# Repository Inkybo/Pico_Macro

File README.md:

# Pico_Macro Keypad

Pico_Macro is 3*2 keys plus two rotary encoders w/ push button as well as a 128x32 OLED screen and trackball. 

## Firmware

Pico_Macro uses [KMK firmware](http://kmkfw.info)

The code.py file contains a basic template for configureing the keys and the optional pimoroni trackback

## Images

The bare pcb: 

Populated board

/w Keys 

## TODO

- [x] add pictures to readme
- [ ] configure screen to work
- [ ] add support for kailh choc

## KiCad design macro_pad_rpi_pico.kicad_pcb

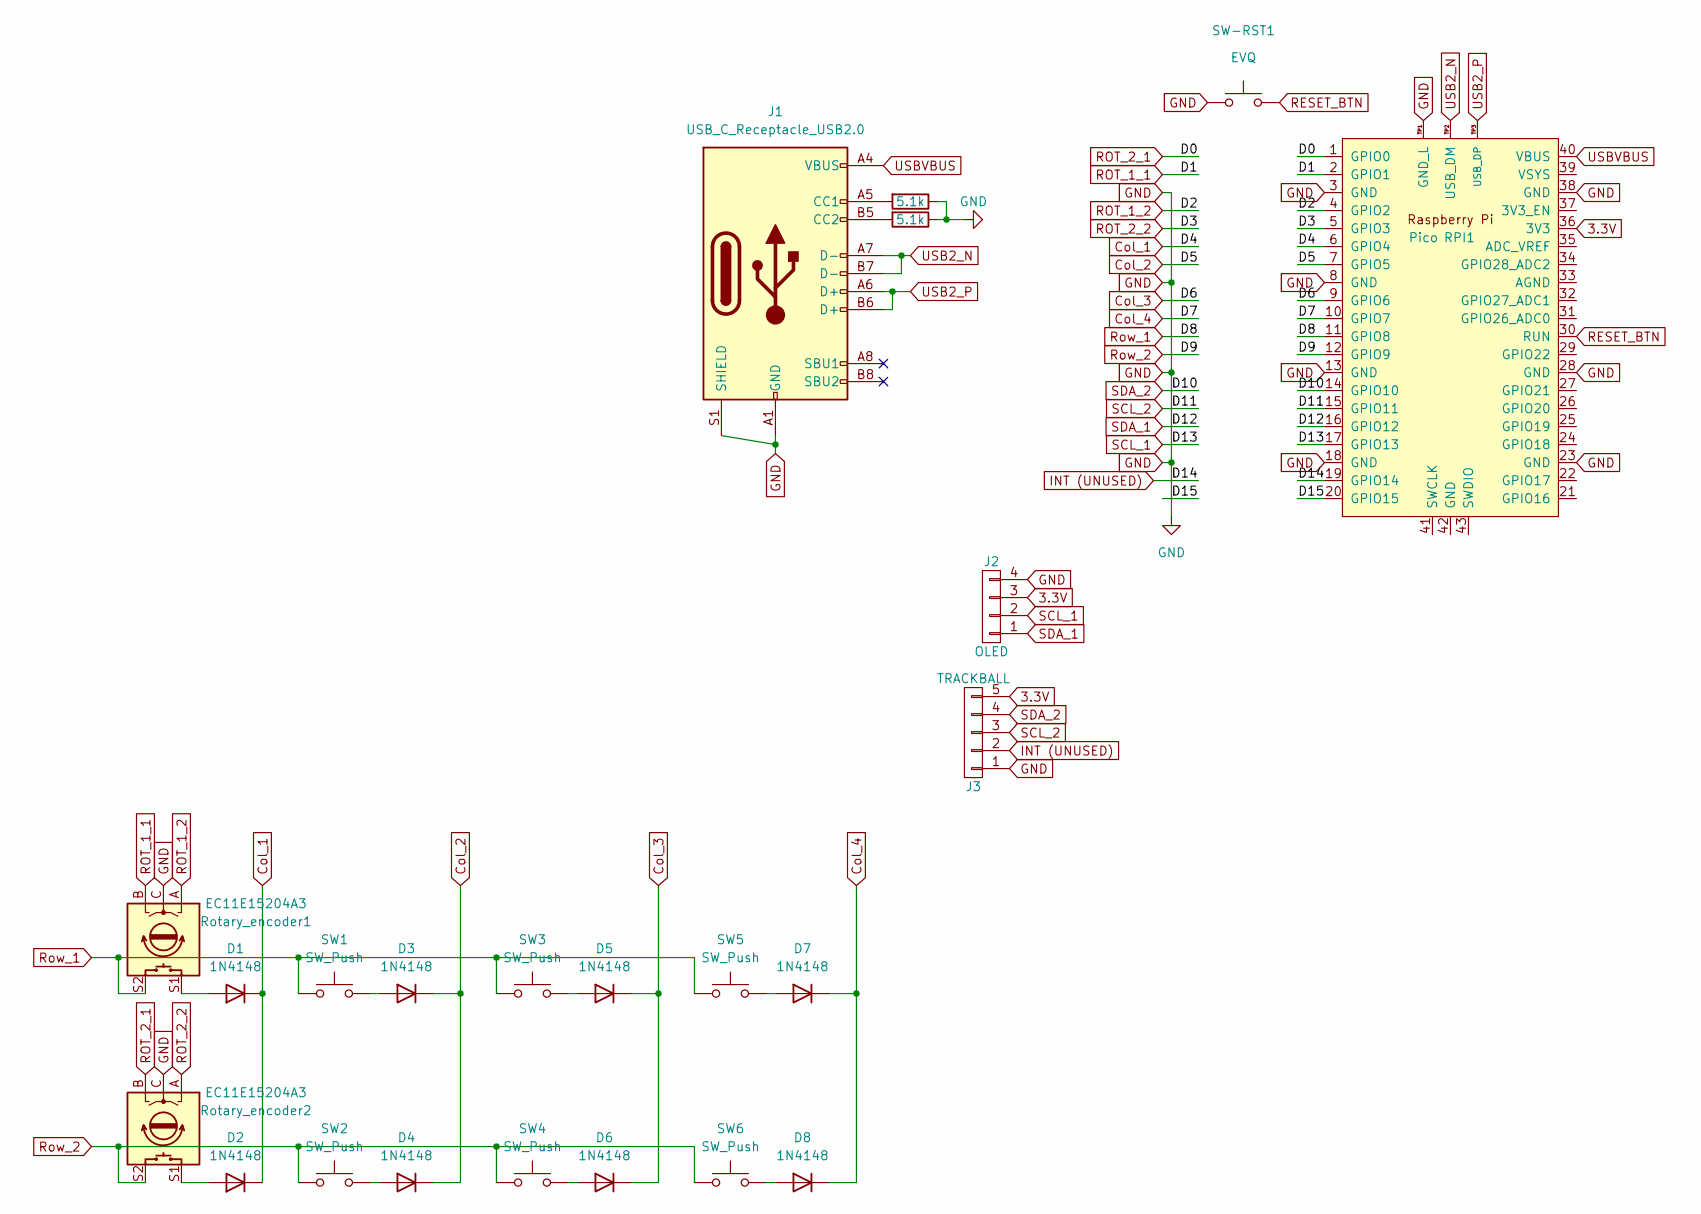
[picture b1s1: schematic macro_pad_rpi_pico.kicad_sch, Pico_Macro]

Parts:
D1, D2, D3, D4, D5, D6, D7, D8: 1N4148; D_DO-35_SOD27_P7.62mm_Horizontal
J1: USB_C_Receptacle_USB2.0; USB_C_GCT_USB4085
J2: OLED; OLED_4Pin
J3: TRACKBALL; OLED_5Pin
R1, R2: 5.1k; R_Axial_DIN0207_L6.3mm_D2.5mm_P7.62mm_Horizontal
RPI1: Pico; RPi_Pico_SMD_TH
Rotary_encoder1, Rotary_encoder2: EC11E15204A3; RotaryEncoder_Alps_EC11E-Switch_Vertical_H20mm-keebio_modif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
SW1, SW2, SW3, SW4, SW5, SW6: SW_Push; SW_Cherry_MX_PCB_1.00u
SW-RST1: EVQ; TACT_SWITCH_TVBP06

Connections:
3.3V: J2.3, J3.5, RPI1.36 (3V3)
/D15: RPI1.20 (GPIO15)
Col_1: D1.1 (K), D2.1 (K), RPI1.6 (GPIO4)
Col_2: D3.1 (K), D4.1 (K), RPI1.7 (GPIO5)
Col_3: D5.1 (K), D6.1 (K), RPI1.9 (GPIO6)
Col_4: D7.1 (K), D8.1 (K), RPI1.10 (GPIO7)
GND: J1.A1 (GND), J1.A12 (GND), J1.B1 (GND), J1.B12 (GND), J1.S1 (SHIELD), J2.4, J3.1, R1.1, R2.1, RPI1.3 (GND), RPI1.8 (GND), RPI1.13 (GND), RPI1.18 (GND), RPI1.23 (GND), RPI1.28 (GND), RPI1.38 (GND), RPI1.TP1 (GND_L), Rotary_encoder1.C, Rotary_encoder2.C, SW-RST1.1
INT (UNUSED): J3.2, RPI1.19 (GPIO14)
unnamed: D1.2 (A), Rotary_encoder1.S1
unnamed: D2.2 (A), Rotary_encoder2.S1
unnamed: D3.2 (A), SW1.2
unnamed: D4.2 (A), SW2.2
unnamed: D5.2 (A), SW3.2
unnamed: D6.2 (A), SW4.2
unnamed: D7.2 (A), SW5.2
unnamed: D8.2 (A), SW6.2
unnamed: J1.A5 (CC1), R1.2
unnamed: J1.B5 (CC2), R2.2
RESET_BTN: RPI1.30 (RUN), SW-RST1.2
ROT_1_1: RPI1.2 (GPIO1), Rotary_encoder1.B
ROT_1_2: RPI1.4 (GPIO2), Rotary_encoder1.A
ROT_2_1: RPI1.1 (GPIO0), Rotary_encoder2.B
ROT_2_2: RPI1.5 (GPIO3), Rotary_encoder2.A
Row_1: RPI1.11 (GPIO8), Rotary_encoder1.S2, SW1.1, SW3.1, SW5.1
Row_2: RPI1.12 (GPIO9), Rotary_encoder2.S2, SW2.1, SW4.1, SW6.1
SCL_1: J2.2, RPI1.17 (GPIO13)
SCL_2: J3.3, RPI1.15 (GPIO11)
SDA_1: J2.1, RPI1.16 (GPIO12)
SDA_2: J3.4, RPI1.14 (GPIO10)
USB2_N: J1.A7 (D-), J1.B7 (D-), RPI1.TP2 (USB_DM)
USB2_P: J1.A6 (D+), J1.B6 (D+), RPI1.TP3 (USB_DP)
USBVBUS: J1.A4 (VBUS), J1.A9 (VBUS), J1.B4 (VBUS), J1.B9 (VBUS), RPI1.40 (VBUS)

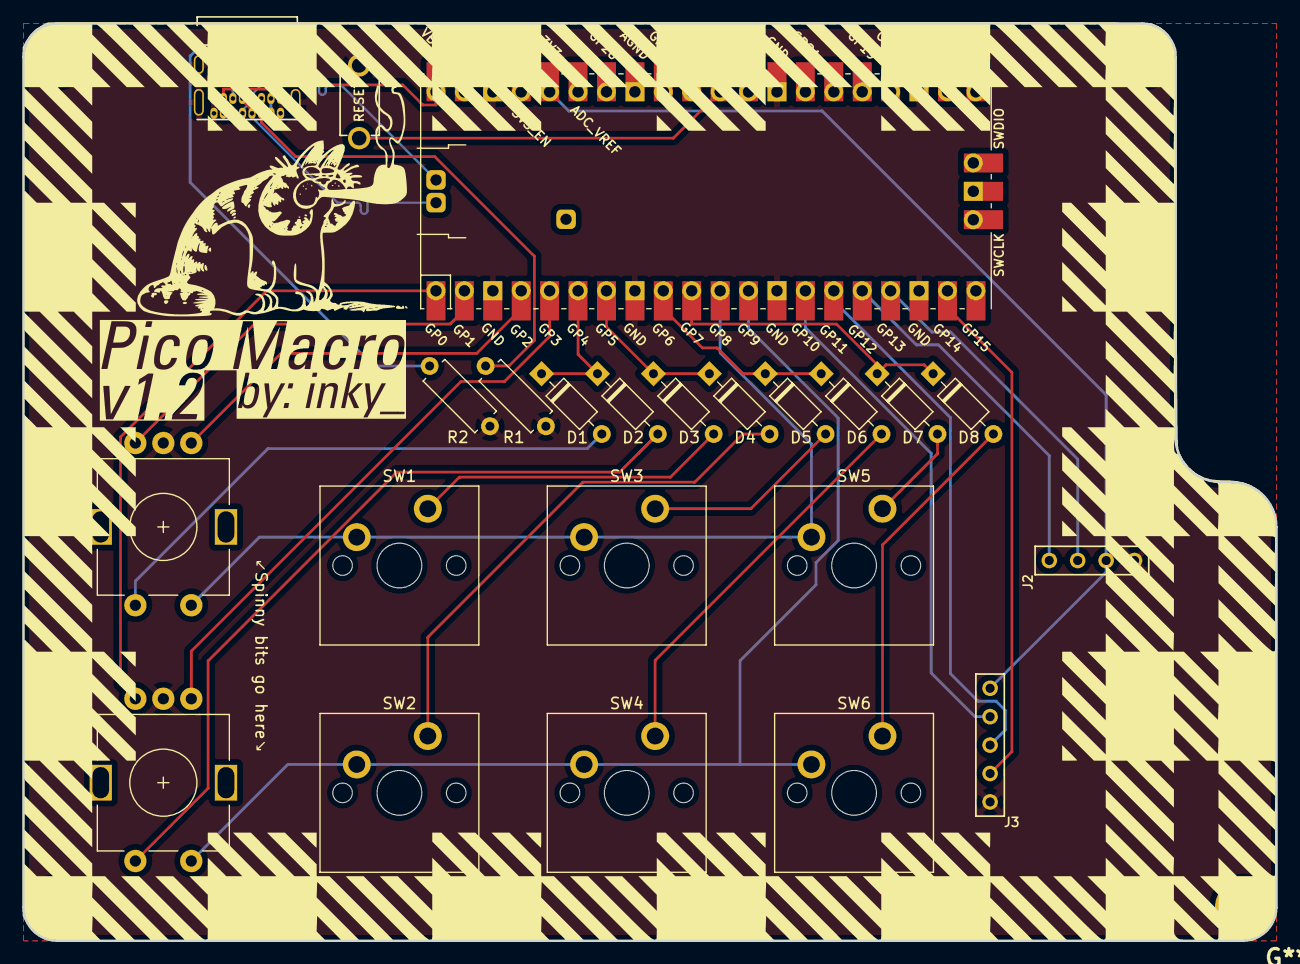
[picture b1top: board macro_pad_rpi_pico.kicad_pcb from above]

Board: 2 copper layers, 112.0 x 82.0 mm, 27 parts (0 on the bottom side), 31 nets.

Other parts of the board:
REF1, REF2, REF4: MountingHole_2.5mm_Pad
REF3: 2.5mm_Pad; MountingHole_2.5mm_Pad

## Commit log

2022-09-23 added board image
2023-01-15 cleaned up files
2023-01-15 cleaned up filenames
